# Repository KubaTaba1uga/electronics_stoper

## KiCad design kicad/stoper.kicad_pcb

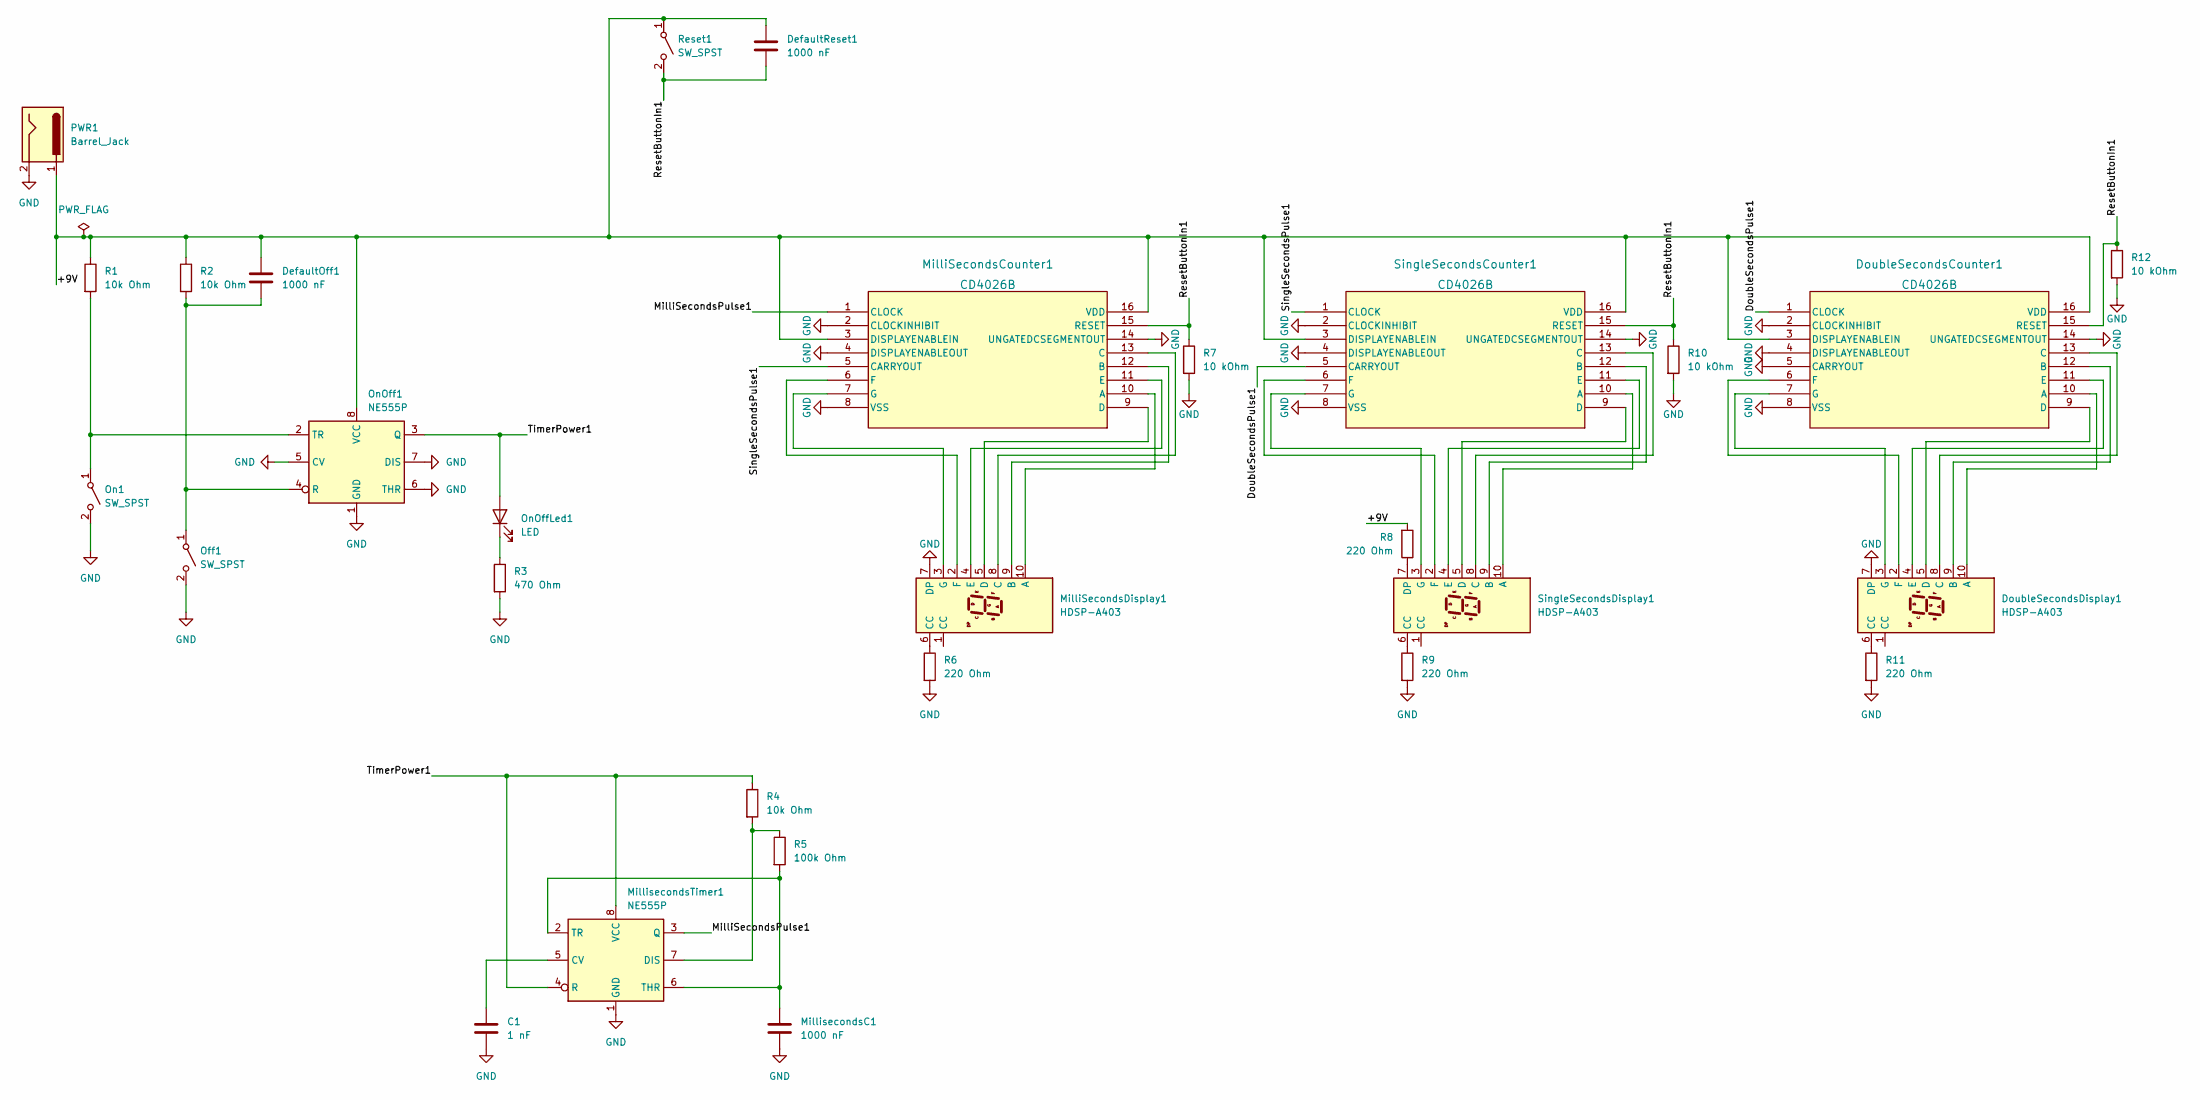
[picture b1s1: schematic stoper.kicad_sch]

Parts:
C1: 1 nF; CP_Radial_D5.0mm_P2.50mm
DefaultOff1: 1000 nF; CP_Radial_D8.0mm_P5.00mm
DefaultReset1: 1000 nF; CP_Radial_D8.0mm_P5.00mm
DoubleSecondsCounter1: CD4026B; DIP-16_W10.16mm
DoubleSecondsDisplay1: HDSP-A403; 7SegmentLED_LTS6760_LTS6780
MilliSecondsCounter1: CD4026B; DIP-16_W10.16mm
MilliSecondsDisplay1: HDSP-A403; 7SegmentLED_LTS6760_LTS6780
MillisecondsC1: 1000 nF; CP_Radial_D8.0mm_P5.00mm
MillisecondsTimer1: NE555P; DIP-8_W7.62mm
Off1: SW_SPST; SW_PUSH_6mm
On1: SW_SPST; SW_PUSH_6mm
OnOff1: NE555P; DIP-8_W7.62mm
OnOffLed1: LED; LED_D5.0mm
PWR1: Barrel_Jack; BarrelJack_GCT_DCJ200-10-A_Horizontal
R1, R2, R4: 10k Ohm; R_Axial_DIN0207_L6.3mm_D2.5mm_P10.16mm_Horizontal
R3: 470 Ohm; R_Axial_DIN0207_L6.3mm_D2.5mm_P10.16mm_Horizontal
R5: 100k Ohm; R_Axial_DIN0207_L6.3mm_D2.5mm_P10.16mm_Horizontal
R6, R8, R9, R11: 220 Ohm; R_Axial_DIN0207_L6.3mm_D2.5mm_P10.16mm_Horizontal
R7, R10, R12: 10 kOhm; R_Axial_DIN0207_L6.3mm_D2.5mm_P10.16mm_Horizontal
Reset1: SW_SPST; SW_PUSH_6mm
SingleSecondsCounter1: CD4026B; DIP-16_W10.16mm
SingleSecondsDisplay1: HDSP-A403; 7SegmentLED_LTS6760_LTS6780

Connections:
/+9V: DefaultOff1.1, DefaultReset1.1, DoubleSecondsCounter1.3 (DISPLAYENABLEIN), DoubleSecondsCounter1.16 (VDD), MilliSecondsCounter1.3 (DISPLAYENABLEIN), MilliSecondsCounter1.16 (VDD), OnOff1.8 (VCC), PWR1.1, R1.1, R2.1, R8.2, Reset1.1 (A), SingleSecondsCounter1.3 (DISPLAYENABLEIN), SingleSecondsCounter1.16 (VDD)
/DoubleSecondsPulse1: DoubleSecondsCounter1.1 (CLOCK), SingleSecondsCounter1.5 (CARRYOUT)
/MilliSecondsPulse1: MilliSecondsCounter1.1 (CLOCK), MillisecondsTimer1.3 (Q)
/ResetButtonIn1: DefaultReset1.2, DoubleSecondsCounter1.15 (RESET), MilliSecondsCounter1.15 (RESET), R7.1, R10.1, R12.1, Reset1.2 (B), SingleSecondsCounter1.15 (RESET)
/SingleSecondsPulse1: MilliSecondsCounter1.5 (CARRYOUT), SingleSecondsCounter1.1 (CLOCK)
/TimerPower1: MillisecondsTimer1.4 (R), MillisecondsTimer1.8 (VCC), OnOff1.3 (Q), OnOffLed1.2 (A), R4.1
GND: C1.2, DoubleSecondsCounter1.2 (CLOCKINHIBIT), DoubleSecondsCounter1.4 (DISPLAYENABLEOUT), DoubleSecondsCounter1.5 (CARRYOUT), DoubleSecondsCounter1.8 (VSS), DoubleSecondsCounter1.14 (UNGATEDCSEGMENTOUT), DoubleSecondsDisplay1.7 (DP), MilliSecondsCounter1.2 (CLOCKINHIBIT), MilliSecondsCounter1.4 (DISPLAYENABLEOUT), MilliSecondsCounter1.8 (VSS), MilliSecondsCounter1.14 (UNGATEDCSEGMENTOUT), MilliSecondsDisplay1.7 (DP), MillisecondsC1.2, MillisecondsTimer1.1 (GND), Off1.2 (B), On1.2 (B), OnOff1.1 (GND), OnOff1.5 (CV), OnOff1.6 (THR), OnOff1.7 (DIS), PWR1.2, R3.2, R6.2, R7.2, R9.2, R10.2, R11.2, R12.2, SingleSecondsCounter1.2 (CLOCKINHIBIT), SingleSecondsCounter1.4 (DISPLAYENABLEOUT), SingleSecondsCounter1.8 (VSS), SingleSecondsCounter1.14 (UNGATEDCSEGMENTOUT)
unnamed: C1.1, MillisecondsTimer1.5 (CV)
unnamed: DefaultOff1.2, Off1.1 (A), OnOff1.4 (R), R2.2
unnamed: DoubleSecondsCounter1.6 (F), DoubleSecondsDisplay1.2 (F)
unnamed: DoubleSecondsCounter1.7 (G), DoubleSecondsDisplay1.3 (G)
unnamed: DoubleSecondsCounter1.9 (D), DoubleSecondsDisplay1.5 (D)
unnamed: DoubleSecondsCounter1.10 (A), DoubleSecondsDisplay1.10 (A)
unnamed: DoubleSecondsCounter1.11 (E), DoubleSecondsDisplay1.4 (E)
unnamed: DoubleSecondsCounter1.12 (B), DoubleSecondsDisplay1.9 (B)
unnamed: DoubleSecondsCounter1.13 (C), DoubleSecondsDisplay1.8 (C)
unnamed: DoubleSecondsDisplay1.6 (CC), R11.1
unnamed: MilliSecondsCounter1.6 (F), MilliSecondsDisplay1.2 (F)
unnamed: MilliSecondsCounter1.7 (G), MilliSecondsDisplay1.3 (G)
unnamed: MilliSecondsCounter1.9 (D), MilliSecondsDisplay1.5 (D)
unnamed: MilliSecondsCounter1.10 (A), MilliSecondsDisplay1.10 (A)
unnamed: MilliSecondsCounter1.11 (E), MilliSecondsDisplay1.4 (E)
unnamed: MilliSecondsCounter1.12 (B), MilliSecondsDisplay1.9 (B)
unnamed: MilliSecondsCounter1.13 (C), MilliSecondsDisplay1.8 (C)
unnamed: MilliSecondsDisplay1.6 (CC), R6.1
unnamed: MillisecondsC1.1, MillisecondsTimer1.2 (TR), MillisecondsTimer1.6 (THR), R5.2
unnamed: MillisecondsTimer1.7 (DIS), R4.2, R5.1
unnamed: On1.1 (A), OnOff1.2 (TR), R1.2
unnamed: OnOffLed1.1 (K), R3.1
unnamed: R8.1, SingleSecondsDisplay1.7 (DP)
unnamed: R9.1, SingleSecondsDisplay1.6 (CC)
unnamed: SingleSecondsCounter1.6 (F), SingleSecondsDisplay1.2 (F)
unnamed: SingleSecondsCounter1.7 (G), SingleSecondsDisplay1.3 (G)
unnamed: SingleSecondsCounter1.9 (D), SingleSecondsDisplay1.5 (D)
unnamed: SingleSecondsCounter1.10 (A), SingleSecondsDisplay1.10 (A)
unnamed: SingleSecondsCounter1.11 (E), SingleSecondsDisplay1.4 (E)
unnamed: SingleSecondsCounter1.12 (B), SingleSecondsDisplay1.9 (B)
unnamed: SingleSecondsCounter1.13 (C), SingleSecondsDisplay1.8 (C)

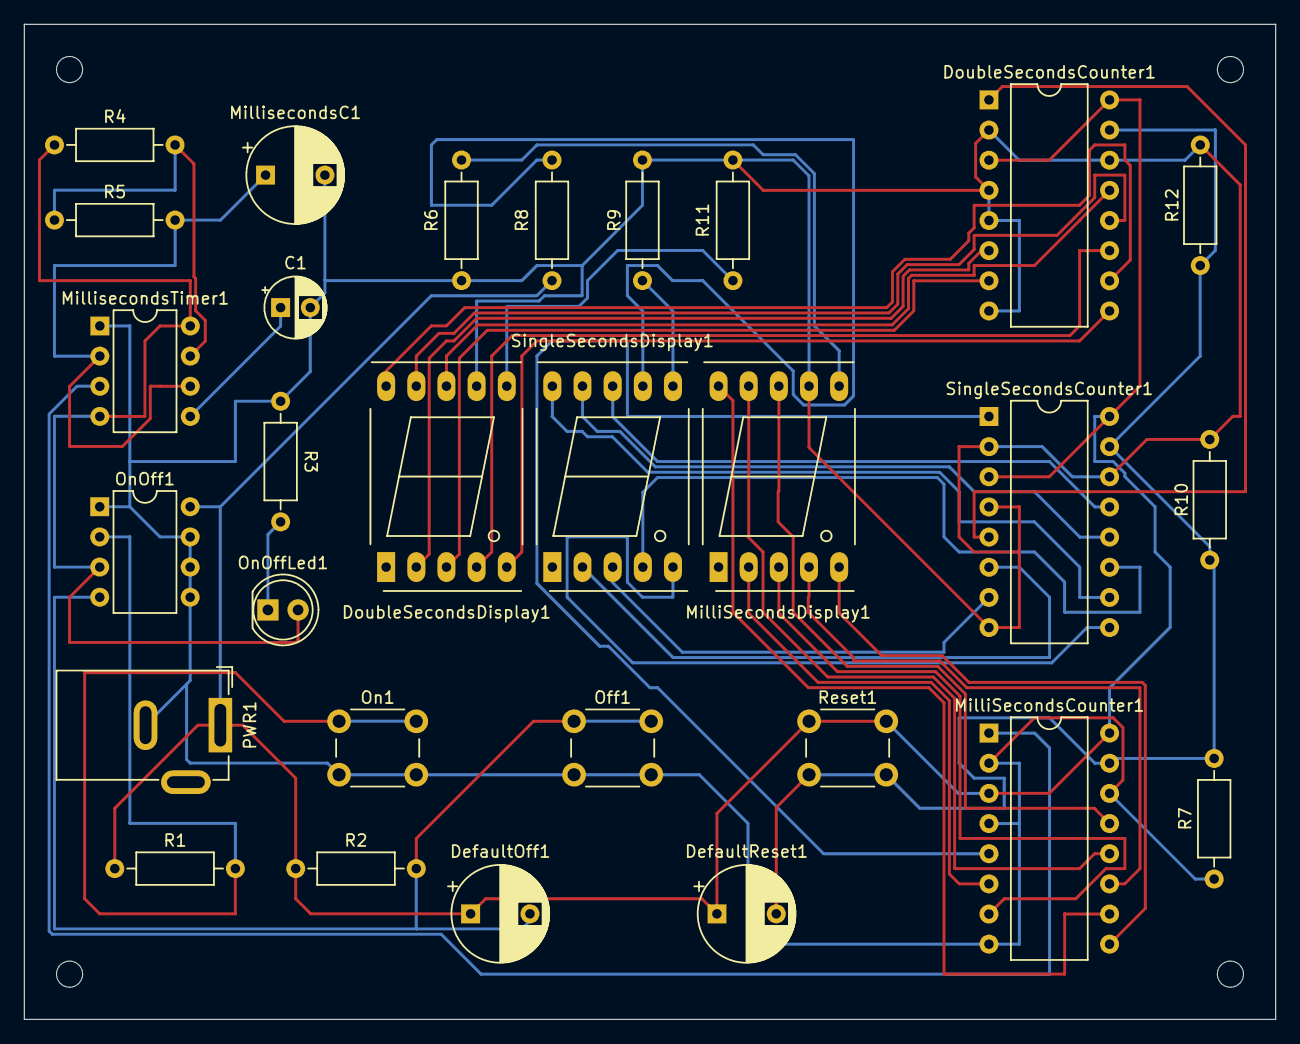
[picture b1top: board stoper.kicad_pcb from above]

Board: 2 copper layers, 105.4 x 83.8 mm, 33 parts (0 on the bottom side), 38 nets.

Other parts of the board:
REF1, REF2, REF3, REF4: MountingHole_2.2mm_M2

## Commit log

2024-09-24 add fritzing project
2024-09-24 finish breadboard and add schematics
2024-09-27 fix bugs in schematics
2024-09-27 fix bugs in breadboard
2024-09-27 fix bugs in breadboard and schematics
2024-09-27 reset stoper when switched on
2024-09-27 stop counting when stoper switched on
2024-10-03 add kicad project to repo
2024-10-03 add kicad schematics draft
2024-10-03 finish up stoper schematics in kicad
2024-10-03 update stoper schematics in kicad
2024-10-05 assign footprints to kicad proj
2024-10-05 improve footprints in kicad proj
2024-10-08 save pcb layout draft
2024-10-08 save pcb layout draft v3, wiring finished
2024-10-10 finish designing pcb
